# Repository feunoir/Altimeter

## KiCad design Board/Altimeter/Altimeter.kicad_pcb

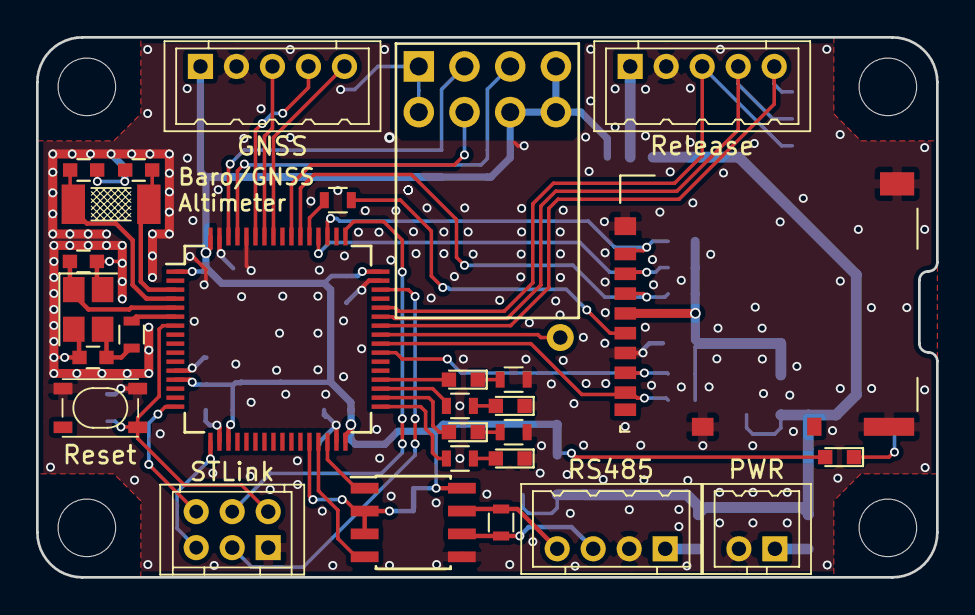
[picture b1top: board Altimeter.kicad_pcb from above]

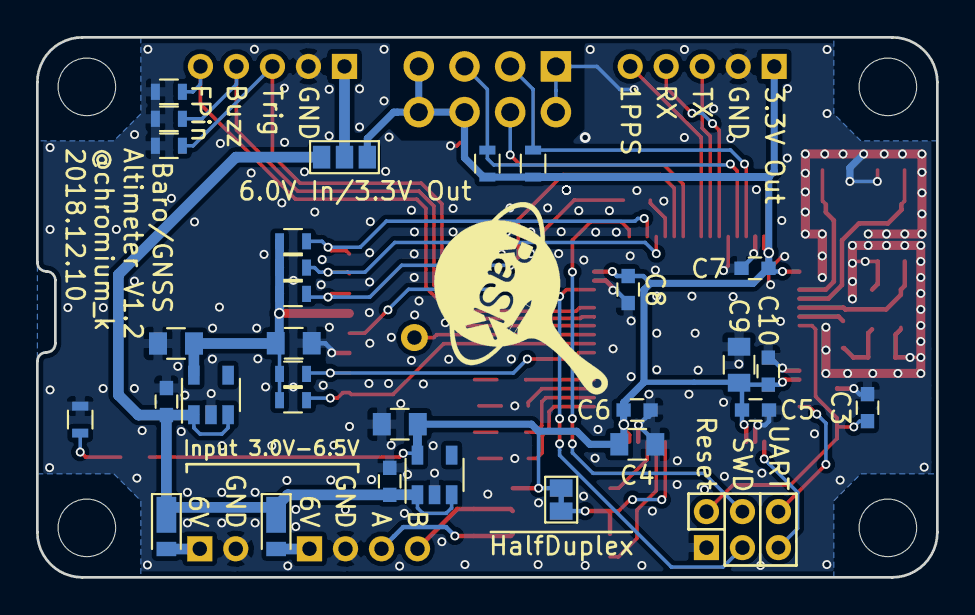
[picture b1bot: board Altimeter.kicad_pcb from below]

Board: 2 copper layers, 50.0 x 30.0 mm, 59 parts (30 on the bottom side), 48 nets.

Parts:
C1, C3, C5, C6, C7, C8, C16: 0.1u; C_0603
C2, C17: 0.47u; C_0805
C4: 4.7u; C_0805
C9, C15: 1u; C_0805
C10: 0.01u; C_0603
C11, C12, C13, C14: 12p; C_0603
D1: PWR; LED_0603
D2: LED_R; LED_0603
D3: LED_Y; LED_0603
D4: LED_G; LED_0603
D5: LED_B; LED_0603
D6, D7: RSX101VA; D_TUMD2
J1: PWRIN; DF3A-2P-2DSA
J2: STLink; DF11-6DP-2DSA
J3: Micro_SD_Card_Det_Hirose_DM3AT; microSD_Card_Receptacle_Hirose_DM3AT-SF-PEJM5
J4: GNSS; DF3A-5P-2DSA
J5: RS485; DF3A-4P-2DSA
J6: ReleaseSys; DF3A-5P-2DSA
JP1: ~HalfDuplex; GS2-Bridged
JP2: 6VIN/3.3VOUT; GS3
R1, R2, R3, R4, R5: 300; R_0603
R6: 80; R_0603
R7, R8, R9, R10, R11: 22k; R_0603
R12: 0-47; R_0603
R13: 120; R_0603
R14, R15, R16, R17, R18: 10k; R_0603
SW1: SW_RESET; SW_SPST_SKRPACE010
TP1: MCO; Measurement_Point_Round-TH_Small
U1: STM32L431RBTx; LQFP-64_10x10mm_Pitch0.5mm
U2: LPS22HB_Module; Strawberry-Linux_Module_8P_NoHole
U3: ST1480AxDR; SOIC-8_3.9x4.9mm_Pitch1.27mm
VR1, VR2: NJM12888; SOT-23-5
Y1: FA238-20MHz; Crystal_SMD_SeikoEpson_FA238-4pin_3.2x2.5mm
Y2: FC255-32.768kHz; Crystal_SMD_SeikoEpson_FC255-2pin_4.9x1.8mm

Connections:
+3V3: C2.1, C4.1, C5.1, C6.1, C7.1, C8.1, C9.1, C10.1, D1.2, J4.1, JP1.1, JP2.3, R14.1, R15.1, U1.1, U1.13, U1.19, U1.32, U1.48, U1.64, U2.4, U2.7, U2.8, U3.8, VR1.5
+6V: C1.1, C16.1, D6.1, D7.1, JP2.1, VR1.1, VR1.3, VR2.1, VR2.3
/BUZZER: J6.4, R17.1, U1.43
/DEBUG_RX: J2.5, U1.17
/DEBUG_TX: J2.6, U1.16
/FLIGHTPIN: J6.5, R18.1, U1.42
/GNSS_1PPS: J4.5, U1.57
/GNSS_RX: J4.4, U1.59
/GNSS_TX: J4.3, U1.58
/HSE_IN: C11.1, U1.5, Y1.1
/HSE_OUT: R6.1, U1.6
/I2C1_SCL: R15.2, U1.61, U2.3
/I2C1_SDA: R14.2, U1.62, U2.2
/LED_B: R2.2, U1.33
/LED_G: D3.2, U1.34
/LED_R: D5.2, U1.36
/LED_Y: R4.2, U1.35
/LPS22HB_INT: U1.55, U2.6
/LSE_IN: C13.1, U1.3, Y2.1
/LSE_OUT: C14.1, U1.4, Y2.2
/RESET: C3.1, J2.2, SW1.1, U1.7
/RS485_EN: JP1.2, U1.28, U3.2, U3.3
/RS485_RX: U1.30, U3.1
/RS485_TX: U1.29, U3.4
/SD_CLK: R12.2, U1.53
/SD_CMD: J3.3, R9.2, U1.54
/SD_DAT0: J3.7, R10.2, U1.39
/SD_DAT1: J3.8, R11.2, U1.40
/SD_DAT2: J3.1, R7.2, U1.51
/SD_DAT3: J3.2, R8.2, U1.52
/SWCLK: J2.4, U1.49
/SWDIO: J2.3, U1.46
/TRIGGER: J6.3, R16.1, U1.44
GND: C1.2, C2.2, C3.2, C4.2, C5.2, C6.2, C7.2, C8.2, C9.2, C10.2, C11.2, C12.2, C13.2, C14.2, C15.2, C16.2, C17.2, D2.1, D4.1, J1.2, J2.1, J3.6, J3.11, J4.2, J5.2, J6.2, R1.2, R3.1, R5.1, R16.2, R17.2, R18.2, SW1.3, SW1.4, U1.12, U1.18, U1.31, U1.47, U1.60, U1.63, U2.1, U2.5, U3.5, VR1.2, VR2.2, Y1.2, Y1.4
unnamed: C12.1, R6.2, Y1.3
unnamed: D1.1, R1.1
unnamed: D2.2, R2.1
unnamed: D3.1, R3.2
unnamed: D4.2, R4.1
unnamed: D5.1, R5.2
unnamed: D6.2, J1.1
unnamed: D7.2, J5.1
unnamed: J3.5, R12.1
unnamed: J5.3, R13.1, U3.6
unnamed: J5.4, R13.2, U3.7
unnamed: J6.1, JP2.2
unnamed: TP1.1, U1.41
VDD: C15.1, C17.1, J3.4, R7.1, R8.1, R9.1, R10.1, R11.1, VR2.5

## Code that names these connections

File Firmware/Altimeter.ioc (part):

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Mcu.Name=STM32L431R(B-C)Tx
Mcu.Package=LQFP64
Mcu.UserName=STM32L431RBTx
PA10.Mode=I2C
PA10.Signal=I2C1_SDA
PA13\ (JTMS-SWDIO).Mode=Serial_Wire
PA13\ (JTMS-SWDIO).Signal=SYS_JTMS-SWDIO
PA14\ (JTCK-SWCLK).Mode=Serial_Wire
PA14\ (JTCK-SWCLK).Signal=SYS_JTCK-SWCLK
PA2.GPIOParameters=GPIO_Label
PA2.GPIO_Label=DEBUG_TX
PA2.Mode=Asynchronous
PA2.Signal=USART2_TX
PA3.GPIOParameters=GPIO_Label
PA3.GPIO_Label=DEBUG_RX
PA3.Mode=Asynchronous
PA3.Signal=USART2_RX
PA9.Mode=I2C
PA9.Signal=I2C1_SCL
PB12.Signal=GPIO_Output
PB13.Signal=GPIO_Output
PB14.Signal=GPIO_Output
PB15.Signal=GPIO_Output
PB6.GPIOParameters=GPIO_Label
PB6.GPIO_Label=GPS_TX
PB6.Mode=Asynchronous
PB6.Signal=USART1_TX
PB7.GPIOParameters=GPIO_Label
PB7.GPIO_Label=GPS_RX
PB7.Mode=Asynchronous
PB7.Signal=USART1_RX
PC10.Mode=SD_4_bits_Wide_bus
PC10.Signal=SDMMC1_D2
PC11.Mode=SD_4_bits_Wide_bus
PC11.Signal=SDMMC1_D3
PC12.Mode=SD_4_bits_Wide_bus
PC12.Signal=SDMMC1_CK
PC14-OSC32_IN\ (PC14).Mode=LSE-External-Oscillator
PC14-OSC32_IN\ (PC14).Signal=RCC_OSC32_IN
PC15-OSC32_OUT\ (PC15).Mode=LSE-External-Oscillator
PC15-OSC32_OUT\ (PC15).Signal=RCC_OSC32_OUT
PC4.GPIOParameters=GPIO_Label
PC4.GPIO_Label=RS485_TX
PC4.Mode=Asynchronous
PC4.Signal=USART3_TX
PC5.GPIOParameters=GPIO_Label
PC5.GPIO_Label=RS485_RX
PC5.Mode=Asynchronous
PC5.Signal=USART3_RX
PC8.Mode=SD_4_bits_Wide_bus
PC8.Signal=SDMMC1_D0
PC9.Mode=SD_4_bits_Wide_bus
PC9.Signal=SDMMC1_D1
PD2.Mode=SD_4_bits_Wide_bus
PD2.Signal=SDMMC1_CMD
PH0-OSC_IN\ (PH0).Mode=HSE-External-Oscillator
PH0-OSC_IN\ (PH0).Signal=RCC_OSC_IN
PH1-OSC_OUT\ (PH1).Mode=HSE-External-Oscillator
PH1-OSC_OUT\ (PH1).Signal=RCC_OSC_OUT
RCC.HSE_VALUE=16000000
RCC.SYSCLKFreq_VALUE=80000000
RCC.SYSCLKSource=RCC_SYSCLKSOURCE_PLLCLK

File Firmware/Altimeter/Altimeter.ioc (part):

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Mcu.Name=STM32L431R(B-C)Tx
Mcu.Package=LQFP64
Mcu.UserName=STM32L431RBTx
PA2.GPIOParameters=GPIO_Label
PA2.GPIO_Label=DEBUG_TX
PA2.Mode=Asynchronous
PA2.Signal=USART2_TX
PA3.GPIOParameters=GPIO_Label
PA3.GPIO_Label=DEBUG_RX
PA3.Mode=Asynchronous
PA3.Signal=USART2_RX
PB12.GPIOParameters=GPIO_Label
PB12.GPIO_Label=LED_BLUE
PB12.Signal=GPIO_Output
PB13.GPIOParameters=GPIO_Label
PB13.GPIO_Label=LED_GREEN
PB13.Signal=GPIO_Output
PB14.GPIOParameters=GPIO_Label
PB14.GPIO_Label=LED_YELLOW
PB14.Signal=GPIO_Output
PB15.GPIOParameters=GPIO_Label
PB15.GPIO_Label=LED_RED
PB15.Signal=GPIO_Output
PB6.GPIOParameters=GPIO_Label
PB6.GPIO_Label=GNSS_TX
PB6.Mode=Asynchronous
PB6.Signal=USART1_TX
PB7.GPIOParameters=GPIO_Label
PB7.GPIO_Label=GNSS_RX
PB7.Mode=Asynchronous
PB7.Signal=USART1_RX
PB8.Mode=I2C
PB8.Signal=I2C1_SCL
PB9.Mode=I2C
PB9.Signal=I2C1_SDA
PC10.Mode=SD_4_bits_Wide_bus
PC10.Signal=SDMMC1_D2
PC11.Mode=SD_4_bits_Wide_bus
PC11.Signal=SDMMC1_D3
PC12.Mode=SD_4_bits_Wide_bus
PC12.Signal=SDMMC1_CK
PC14-OSC32_IN\ (PC14).Mode=LSE-External-Oscillator
PC14-OSC32_IN\ (PC14).Signal=RCC_OSC32_IN
PC15-OSC32_OUT\ (PC15).Mode=LSE-External-Oscillator
PC15-OSC32_OUT\ (PC15).Signal=RCC_OSC32_OUT
PC8.Mode=SD_4_bits_Wide_bus
PC8.Signal=SDMMC1_D0
PC9.Mode=SD_4_bits_Wide_bus
PC9.Signal=SDMMC1_D1
PD2.Mode=SD_4_bits_Wide_bus
PD2.Signal=SDMMC1_CMD
PH0-OSC_IN\ (PH0).Mode=HSE-External-Oscillator
PH0-OSC_IN\ (PH0).Signal=RCC_OSC_IN
PH1-OSC_OUT\ (PH1).Mode=HSE-External-Oscillator
PH1-OSC_OUT\ (PH1).Signal=RCC_OSC_OUT
RCC.HSE_VALUE=16000000
RCC.SYSCLKFreq_VALUE=80000000
RCC.SYSCLKSource=RCC_SYSCLKSOURCE_PLLCLK
board=Altimeter

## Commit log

2018-07-24 complete drawing rough schematic (at this moment) note: can't attach 3dmodel of df11 (because of copyright)
2018-07-24 update .gitignore add pdf schematic file
2018-07-24 corrected a footprint of U1(MCU)
2018-07-24 Revert "corrected a footprint of U1(MCU)"
    This reverts commit f3f174c020a9807a48c6b970d7964ee77ef599ca.
2018-07-24 corrected and changed two footprints
2018-07-29 almost complete(size:40x40)
2018-07-29 almost complete (size:50x30) task: silk and via
2018-08-07 minor update and bug fix
2018-08-10 [Altimeter V1.0] add silk of team logo and imprint add gerber files
2018-08-27 [Altimeter V1.1] invert TX/RX pins of GNSS Connector
2018-08-28 [Altimeter V1.1] connect PH3(BOOT0) to GND add wire between INT_DRDY and MCU
2018-09-06 firmware - first commit
2018-09-08 wrote initial processes -add uart wrapper(xprintf) -add uart_rx_dma.h -add LPS22HB lib -wrote a Initialize function
2018-09-10 add uart rx dma function implemented sd mount&file open functions implemented a timer interrupt routine for collect sensor data
2018-12-09 [Altimeter V1.2] Added another power input way at J6 and added a solder jumper to switch 3V Output / 6V Input.
2019-02-17 [fw.Altimeter_HSE20] create project for HSE20MHz board the board which is written this firmware will start sampling with launching (triggered by triggerpin)
2019-02-17 [fw.Altimeter_HSE20] change EXTI pin name 'LAUNCHDETECT_EXTI' and build project (and bug fix)
2019-03-10 [fw.MGS-01] made a rocket data and deploy management system (rocket.h) add timer for deploy-lock(TIM16) and count-down-deploy (TIM15)
2019-03-10 [fw.MGS-01] delete unnecessary comment outed lines on rocket.c
2019-03-11 [fw.MGS-01] disable GNSS sentence logging add sd writing process add Rocket_GetQueue() to rocket.h
2019-03-11 [fw.MGS-01] add 2ndStage deploy management system to rocket.h and main() loop label trigger signal out pins
2019-03-12 [fw.MGS-01] fix bug around pointer to Rocket_Info_t in rocket.h
2019-03-13 [fw.MGS-01] add code for system log launch-detect-EXTI→it'll be work only once
2019-03-13 [fw.MGS-01] add led indication (deploy trigger and deploy lock)
2019-03-13 fix inverted output of indicator led
2019-03-13 fix flag check bug
2019-03-13 fix bug (enable IRQ with EXTI, TIM15, TIM16)
2019-03-13 [fw.MGS-01] fix TIM15 Prescalar from 39 to 39999 add evaluate deploy timing with baro data(written by 28)
2019-03-13 [fw.MGS-01] add debug messages for Serial debug add Rocket_GetStatus() to rocket.h
2019-03-13 [fw.MGS-01] add feature for holding ground envdata
2019-03-13 add Rocket_EnvData_GetGroundEnvDataSet()
2019-03-13 [fw.MGS-01] update deploy timing evaluation code by 28 add update-flag clearing before start function of Timer with interrupt
2019-03-17 [fw.MGS-01] add log message output after deploy timing evaluating functions and add tag? like these [flag] or [stat] into log messages for easy log analysys
2019-04-20 [fw.1Hz] create a project
2019-04-20 [fw.1Hz] import project into TrueSTUDIO
2019-04-20 [fw.1Hz] Add lib of fatfs, lps22hb, uartdebug and uart rx dma. And fix bug of lps22hb lib. LPS22HB DRDY config was written in wrong register.
2019-04-21 [fw.1Hz] implement 1Hz pressure and temperature sampling fix lps22hb drdy config bug and clock source config bug (HSE 16 to 20)
2019-04-21 [fw.1Hz] change main clock from 80MHz to 60MHz and clock divider of timestamp(TIM2) from 79 to 59999
